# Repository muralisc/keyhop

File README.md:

# keyhop

Turn any wired USB keyboard into a Bluetooth LE keyboard that can hop between three computers.

An ESP32-S3 acts as a USB host for the keyboard and re-sends every keystroke over Bluetooth LE HID. It stores three host slots, and you switch between them with a key chord, like the multi-device buttons on commercial Bluetooth keyboards.

## Features

- **Any USB boot-protocol keyboard.** No drivers and no software on the computer.
- **Three host slots.** Each slot shows up with its own Bluetooth address and name (`keyhop A3F2 1`, `keyhop A3F2 2`, `keyhop A3F2 3`), so every computer pairs with what it sees as a separate keyboard. `A3F2` is a tag unique to each board (from its chip, printed in the serial log at startup), so several keyhops can be told apart. To choose your own tag (up to 6 characters), flash with `PLATFORMIO_BUILD_FLAGS='-DKEYHOP_TAG=\"desk\"' pio run -t upload`.
- **Chord switching.** The chord is swallowed and never reaches the computer.
- **Per-slot re-pairing.** Forget one slot's host without touching the others.
- **Remembers the last slot** across power cycles. Bonds are kept in flash.
- **LED diagnostics** for USB and Bluetooth state, plus serial logging.

## Key chords

| Chord | Action |
|---|---|
| `Ctrl` + `Alt` + `1` / `2` / `3` | Switch to slot 1 / 2 / 3 (left or right Ctrl/Alt) |
| `Ctrl` + `Alt` + `Shift` + `1` / `2` / `3` | Forget that slot's host and start pairing again |

When you switch slots, keyhop releases any held keys on the old host first.

## Hardware

| Board | Status | Notes |
|---|---|---|
| [Olimex ESP32-S3-DevKit-LiPo](https://www.olimex.com/Products/IoT/ESP32-S3/ESP32-S3-DevKit-LiPo/) | ⏳ Default target, not yet tested on hardware | Keyboard on GPIO19 (D−) / GPIO20 (D+) through a USB-A breakout. Flash and monitor through the **USB-UART** USB-C port (CH340X, auto-reset). |
| Waveshare ESP32-S3-DEV-KIT-N8R8 | ⚠️ USB host does not work | GPIO19/20 are hard-wired to the board's CH334F hub. Bluetooth and the LED code build and run. |

### Wiring (Olimex)

Connect a USB-A female breakout to the board:

| USB-A | ESP32-S3 |
|---|---|
| VBUS | 5V |
| D− | GPIO19 |
| D+ | GPIO20 |
| GND | GND |

The keyboard draws its power from the board's 5V rail.

## Building and flashing

You need [PlatformIO](https://platformio.org/).

```sh
# Olimex (default)
pio run -e olimex -t upload
pio device monitor

# Waveshare: hold BOOT, tap RESET, release BOOT, then
pio run -e waveshare -t upload
```

The firmware runs the ESP32-S3 in USB-OTG mode (`ARDUINO_USB_MODE=0`) so the OTG controller can own GPIO19/20. That means native USB CDC is unavailable, and serial logs go out on UART0 (GPIO43/44) at 115200 baud.

Dependencies (installed by PlatformIO):

- [NimBLE-Arduino](https://github.com/h2zero/NimBLE-Arduino) `^1.4.1`
- [EspUsbHost](https://github.com/tanakamasayuki/EspUsbHost) pinned to `9e658fa`, the last commit before v2. v2 needs Arduino core 3.x and has a different API.

## Pairing

1. Power the board with a keyboard plugged in.
2. Press `Ctrl` + `Alt` + `1` to choose slot 1.
3. On the computer, open the Bluetooth settings and pair with **keyhop XXXX 1** (XXXX is the board's tag). No PIN is needed.
4. Repeat with slots 2 and 3 on other computers.

If a computer forgets the keyboard, or you want to give the slot to a different computer, press `Ctrl` + `Alt` + `Shift` + slot number to clear that slot's bond and pair again.

## LED guide

### Olimex (single green LED)

Listed from highest priority to lowest:

| Pattern | Meaning |
|---|---|
| 1–3 quick blinks, then a pause | Slot number, shown for about 2 s after boot or a slot switch |
| Very fast flicker | USB host stack failed to start (firmware problem) |
| Short blip every second | No USB keyboard detected (check wiring or power) |
| Double blip every second | USB device detected but unusable (for example, a keyboard with a built-in hub) |
| Slow even blink | Keyboard OK, Bluetooth waiting to pair or connect |
| Solid on | Keyboard OK, Bluetooth connected |
| Brief inverted flick | A key report arrived from the keyboard |

### Waveshare (RGB LED)

| Colour | Meaning |
|---|---|
| White flash | Keyboard report received and forwarded |
| Red flash | USB data received, but not a boot-keyboard report |
| Blue | No USB device enumerated |
| Blue flicker | USB host stack failed to start |
| Blue / white alternating | USB device enumerated but no usable interface |
| Green / blue / magenta | Slot 1 / 2 / 3, keyboard idle |

Blinking means Bluetooth is advertising. Solid means a host is connected.

## Limitations

- Only boot-protocol keyboard reports are forwarded: 6-key rollover, no media keys.
- Keyboards with a built-in USB hub (common on models with a USB passthrough port) may not enumerate.
- The battery level is always reported as 100%.
- Caps Lock and other indicator LEDs on the keyboard are not driven from the host.

## License

MIT

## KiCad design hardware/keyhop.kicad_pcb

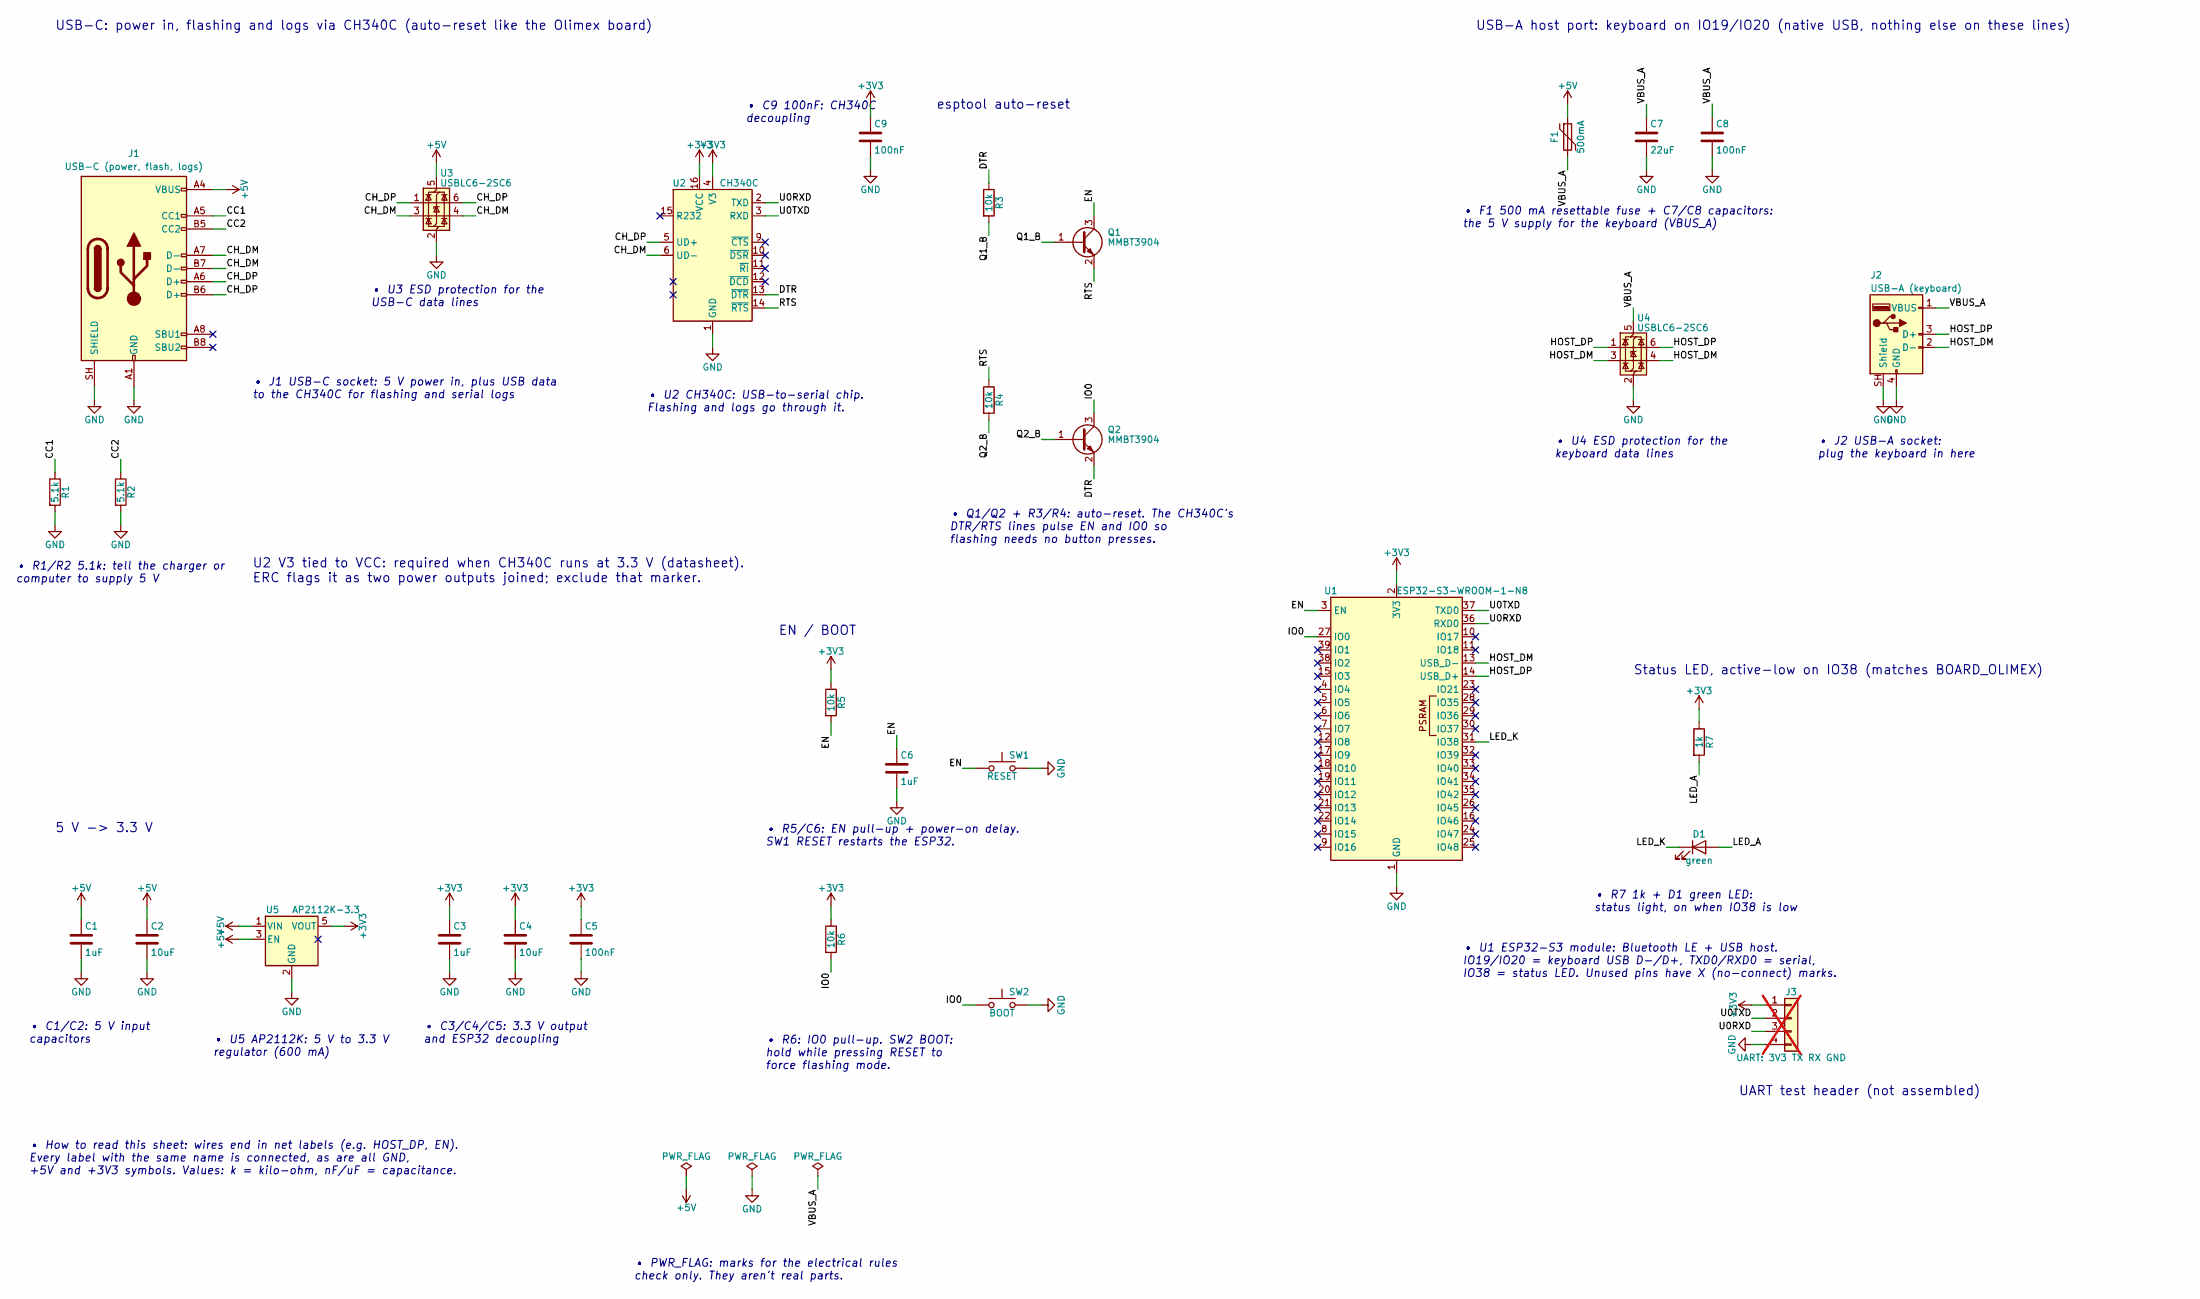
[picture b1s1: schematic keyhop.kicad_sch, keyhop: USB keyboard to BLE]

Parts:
C1, C3, C6: 1uF; C_0603_1608Metric; LCSC C15849
C2, C4: 10uF; C_0603_1608Metric; LCSC C19702
C5, C8, C9: 100nF; C_0603_1608Metric; LCSC C14663
C7: 22uF; C_0805_2012Metric; LCSC C45783
D1: green; LED_0603_1608Metric; LCSC C12624
F1: 500mA; Fuse_1206_3216Metric; LCSC C163512
J1: USB-C (power, flash, logs); USB_C_Receptacle_HRO_TYPE-C-31-M-12; LCSC C165948
J2: USB-A (keyboard); USB_A_Receptacle_XKB_U231-091N-4BLRA00-S; LCSC C2880619
J3: UART: 3V3 TX RX GND; PinHeader_1x04_P2.54mm_Vertical; not fitted
Q1, Q2: MMBT3904; SOT-23; LCSC C20526
R1, R2: 5.1k; R_0603_1608Metric; LCSC C23186
R3, R4, R5, R6: 10k; R_0603_1608Metric; LCSC C25804
R7: 1k; R_0603_1608Metric; LCSC C21190
SW1: RESET; SW_Push_1P1T_XKB_TS-1187A; LCSC C480267
SW2: BOOT; SW_Push_1P1T_XKB_TS-1187A; LCSC C480267
U1: ESP32-S3-WROOM-1-N8; ESP32-S3-WROOM-1; LCSC C2913198
U2: CH340C; SOIC-16_3.9x9.9mm_P1.27mm; LCSC C7464026
U3, U4: USBLC6-2SC6; SOT-23-6; LCSC C7519
U5: AP2112K-3.3; SOT-23-5; LCSC C51118

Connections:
+3V3: C3.1, C4.1, C5.1, C9.1, J3.1, R5.1, R6.1, R7.1, U1.2 (3V3), U2.4 (V3), U2.16 (VCC), U5.5 (VOUT)
+5V: C1.1, C2.1, F1.1, J1.A4 (VBUS), J1.A9 (VBUS), J1.B4 (VBUS), J1.B9 (VBUS), U3.5 (VBUS), U5.1 (VIN), U5.3 (EN)
/CC1: J1.A5 (CC1), R1.1
/CC2: J1.B5 (CC2), R2.1
/CH_DM: J1.A7 (D-), J1.B7 (D-), U2.6 (UD-), U3.3 (I/O2), U3.4 (I/O2)
/CH_DP: J1.A6 (D+), J1.B6 (D+), U2.5 (UD+), U3.1 (I/O1), U3.6 (I/O1)
/DTR: Q2.2 (E), R3.1, U2.13 (~DTR)
/EN: C6.1, Q1.3 (C), R5.2, SW1.1, U1.3 (EN)
/HOST_DM: J2.2 (D-), U1.13 (USB_D-), U4.3 (I/O2), U4.4 (I/O2)
/HOST_DP: J2.3 (D+), U1.14 (USB_D+), U4.1 (I/O1), U4.6 (I/O1)
/IO0: Q2.3 (C), R6.2, SW2.1, U1.27 (IO0)
/LED_A: D1.2 (A), R7.2
/LED_K: D1.1 (K), U1.31 (IO38)
/Q1_B: Q1.1 (B), R3.2
/Q2_B: Q2.1 (B), R4.2
/RTS: Q1.2 (E), R4.1, U2.14 (~RTS)
/U0RXD: J3.3, U1.36 (RXD0), U2.2 (TXD)
/U0TXD: J3.2, U1.37 (TXD0), U2.3 (RXD)
/VBUS_A: C7.1, C8.1, F1.2, J2.1 (VBUS), U4.5 (VBUS)
GND: C1.2, C2.2, C3.2, C4.2, C5.2, C6.2, C7.2, C8.2, C9.2, J1.A1 (GND), J1.A12 (GND), J1.B1 (GND), J1.B12 (GND), J1.SH (SHIELD), J2.4 (GND), J2.SH (Shield), J3.4, R1.2, R2.2, SW1.2, SW2.2, U1.1 (GND), U1.40 (GND), U1.41 (GND), U2.1 (GND), U3.2 (GND), U4.2 (GND), U5.2 (GND)

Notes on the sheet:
USB-A host port: keyboard on IO19/IO20 (native USB, nothing else on these lines)
esptool auto-reset
EN / BOOT
Status LED, active-low on IO38 (matches BOARD_OLIMEX)
U2 V3 tied to VCC: required when CH340C runs at 3.3 V (datasheet). ERC flags it as two power outputs joined; exclude that marker.
5 V -> 3.3 V
UART test header (not assembled)
USB-C: power in, flashing and logs via CH340C (auto-reset like the Olimex board)
• J1 USB-C socket: 5 V power in, plus USB data to the CH340C for flashing and serial logs
• R1/R2 5.1k: tell the charger or computer to supply 5 V
• U3 ESD protection for the USB-C data lines
• U2 CH340C: USB-to-serial chip. Flashing and logs go through it.
• C9 100nF: CH340C decoupling
• Q1/Q2 + R3/R4: auto-reset. The CH340C's DTR/RTS lines pulse EN and IO0 so flashing needs no button presses.
• C1/C2: 5 V input capacitors
• U5 AP2112K: 5 V to 3.3 V regulator (600 mA)
• C3/C4/C5: 3.3 V output and ESP32 decoupling
• R5/C6: EN pull-up + power-on delay. SW1 RESET restarts the ESP32.
• R6: IO0 pull-up. SW2 BOOT: hold while pressing RESET to force flashing mode.
• U1 ESP32-S3 module: Bluetooth LE + USB host. IO19/IO20 = keyboard USB D-/D+, TXD0/RXD0 = serial, IO38 = status LED. Unused pins have X (no-connect) marks.
• R7 1k + D1 green LED: status light, on when IO38 is low
• F1 500 mA resettable fuse + C7/C8 capacitors: the 5 V supply for the keyboard (VBUS_A)
• U4 ESD protection for the keyboard data lines
• J2 USB-A socket: plug the keyboard in here
• PWR_FLAG: marks for the electrical rules check only. They aren't real parts.
• How to read this sheet: wires end in net labels (e.g. HOST_DP, EN). Every label with the same name is connected, as are all GND, +5V and +3V3 symbols. Values: k = kilo-ohm, nF/uF = capacitance.

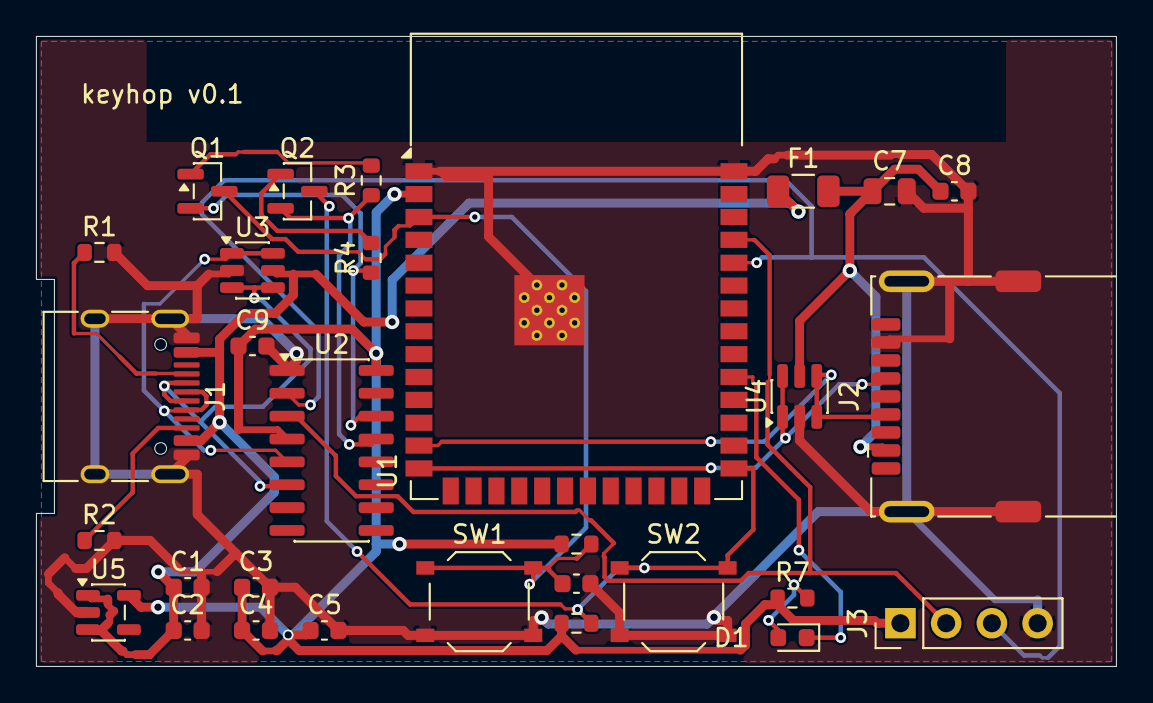
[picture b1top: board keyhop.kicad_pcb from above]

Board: 2 copper layers, 60.0 x 35.0 mm, 30 parts (0 on the bottom side), 20 nets.

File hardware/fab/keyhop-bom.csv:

"Comment","Designator","Footprint","LCSC Part #","Quantity"
"1uF","C1,C3,C6","Capacitor_SMD:C_0603_1608Metric","C15849","3"
"10uF","C2,C4","Capacitor_SMD:C_0603_1608Metric","C19702","2"
"100nF","C5,C8,C9","Capacitor_SMD:C_0603_1608Metric","C14663","3"
"22uF","C7","Capacitor_SMD:C_0805_2012Metric","C45783","1"
"green","D1","LED_SMD:LED_0603_1608Metric","C12624","1"
"500mA","F1","Fuse:Fuse_1206_3216Metric","C163512","1"
"USB-C (power, flash, logs)","J1","Connector_USB:USB_C_Receptacle_HRO_TYPE-C-31-M-12","C165948","1"
"USB-A (keyboard)","J2","Connector_USB:USB_A_Receptacle_XKB_U231-091N-4BLRA00-S","C2880619","1"
"MMBT3904","Q1,Q2","Package_TO_SOT_SMD:SOT-23","C20526","2"
"5.1k","R1,R2","Resistor_SMD:R_0603_1608Metric","C23186","2"
"10k","R3,R4,R5,R6","Resistor_SMD:R_0603_1608Metric","C25804","4"
"1k","R7","Resistor_SMD:R_0603_1608Metric","C21190","1"
"RESET","SW1","Button_Switch_SMD:SW_Push_1P1T_XKB_TS-1187A","C480267","1"
"BOOT","SW2","Button_Switch_SMD:SW_Push_1P1T_XKB_TS-1187A","C480267","1"
"ESP32-S3-WROOM-1-N8","U1","RF_Module:ESP32-S3-WROOM-1","C2913198","1"
"CH340C","U2","Package_SO:SOIC-16_3.9x9.9mm_P1.27mm","C7464026","1"
"USBLC6-2SC6","U3,U4","Package_TO_SOT_SMD:SOT-23-6","C7519","2"
"AP2112K-3.3","U5","Package_TO_SOT_SMD:SOT-23-5","C51118","1"
